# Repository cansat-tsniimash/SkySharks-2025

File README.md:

# SkySharks-2025
Нет, это не про фильм

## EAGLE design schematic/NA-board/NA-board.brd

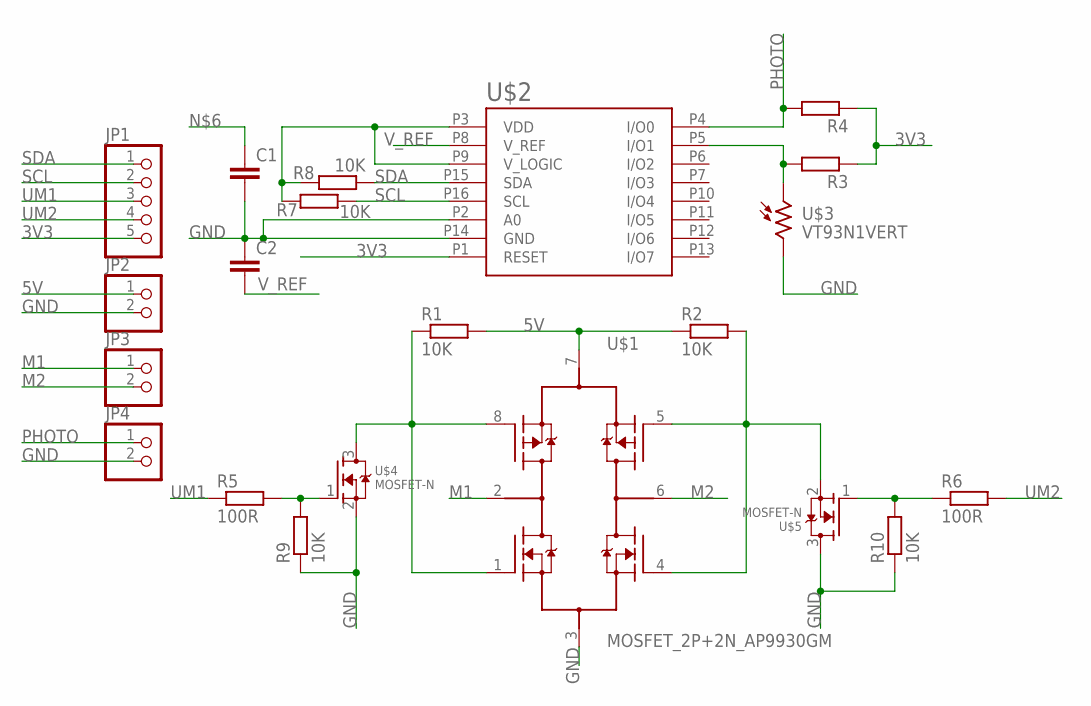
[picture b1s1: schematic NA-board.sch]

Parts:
C1, C2: C-EUC0603; C0603
JP1: PINHD-1X5; 1X05
JP2, JP3, JP4: PINHD-1X2; 1X02
R1, R2, R7, R8, R9, R10: 10K; R0603
R3, R4: R-EU_R0603; R0603
R5, R6: 100R; R0603
U$1: MOSFET_2P+2N_AP9930GM; SO8
U$2: AD5593R
U$3: VT93N1VERT; VT93N1-VERT
U$4, U$5: MOSFET-N; SOT23-3

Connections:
3V3: JP1.5, R3.1, R4.1, R7.2, R8.2, U$2.P1 (RESET), U$2.P3 (VDD), U$2.P9 (V_LOGIC)
5V: JP2.1, R1.2, R2.1, U$1.7 (P1P2S)
GND: C1.2, C2.1, JP2.2, JP4.2, R9.1, R10.1, U$1.3 (N1N2S), U$2.P2 (A0), U$2.P14 (GND), U$3.P$2 (2), U$4.2 (S), U$5.3 (D)
M1: JP3.1, U$1.2 (P1N1D)
M2: JP3.2, U$1.6 (P2N2D)
unnamed: R5.2, R9.2, U$4.1 (G)
unnamed: R2.2, U$1.4 (N2G), U$1.5 (P2G), U$5.2 (S)
unnamed: R1.1, U$1.1 (N1G), U$1.8 (P1G), U$4.3 (D)
unnamed: R3.2, U$2.P5 (I/O1), U$3.P$1 (1)
unnamed: R6.1, R10.2, U$5.1 (G)
PHOTO: JP4.1, R4.2, U$2.P4 (I/O0)
SCL: JP1.2, R7.1, U$2.P16 (SCL)
SDA: JP1.1, R8.1, U$2.P15 (SDA)
UM1: JP1.3, R5.1
UM2: JP1.4, R6.2
V_REF: C2.2, U$2.P8 (V_REF)

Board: 2 copper layers, 21 parts (0 on the bottom side), 16 nets, no tracks yet.

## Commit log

2024-12-07 Сделал структуру репозитория
2024-12-07 Первый раз выгрузл модель CanSat
2024-12-07 Выгрузил первый раз модель спектрометра
2024-12-11 Исправил серву и крепление для неё
2024-12-13 Верхняя часть аппарата
2024-12-14 Сборка Спектрометра
2024-12-14 Заменил батарею, скрыл скелетоны
2024-12-20 Спектрометр с добавлением новых компонентов
2024-12-21 upd. Аппарат
2024-12-21 Созданы шестерни
2024-12-21 Уточнили размеры шестерен
2024-12-21 Новый спектрометр
2024-12-28 Обновлённый спектрометр
2024-12-28 Обновление
2025-01-18 Заменил аккумулятор, уменьшил массу конструкции
2025-01-22 Добавил батарейку 18350
2025-01-31 Почти сделали ГЧ
2025-01-31 3Д-модель. Формат STEP
2025-01-31 Алгоритмы
2025-01-31 Необходимые фото
2025-02-01 Попытался снизить массу, но всё тлен
2025-02-01 Выложили материалы в личный кабинет
2025-02-02 Создали схему печатной платы для спектрометра
2025-02-07 Начинам делать макет для сброса
2025-02-07 Макет спектрометра
2025-02-07 Корпус для тестов парашюта
2025-02-15 Спектрометр
2025-02-22 Меняю крышку под плату спектрометра
2025-03-18 Обновление корпуса
2025-03-18 Готовим модели на печать
2025-03-19 Выгрузил
2025-03-21 Выгрузил заново
2025-04-08 облегчаем модель
2025-04-16 SS Ground
2025-04-29 Правки в модели
2025-05-03 Пытаемся собрать аппарата в живую
